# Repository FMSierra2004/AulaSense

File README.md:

# AulaSense

Repositorio principal para controlar el hardware, firmware y documentación de AulaSense.

## Estado actual

- Hardware: HW 0.1 DRAFT
- Firmware: FW 0.1.0-dev
- Etapa: planificación y prototipo inicial

## Organización

- `hardware/kicad`: esquema y PCB.
- `hardware/libraries`: símbolos y huellas propias.
- `hardware/manufacturing`: entregables para fabricación.
- `firmware`: código fuente del dispositivo.
- `docs`: arquitectura, planificación y compatibilidad.

## Versionado

El hardware utiliza versión y revisión física, por ejemplo `HW 1.0 Rev A`.

El firmware utiliza versiones `MAYOR.MENOR.CORRECCIÓN`, por ejemplo `FW 1.2.3`.

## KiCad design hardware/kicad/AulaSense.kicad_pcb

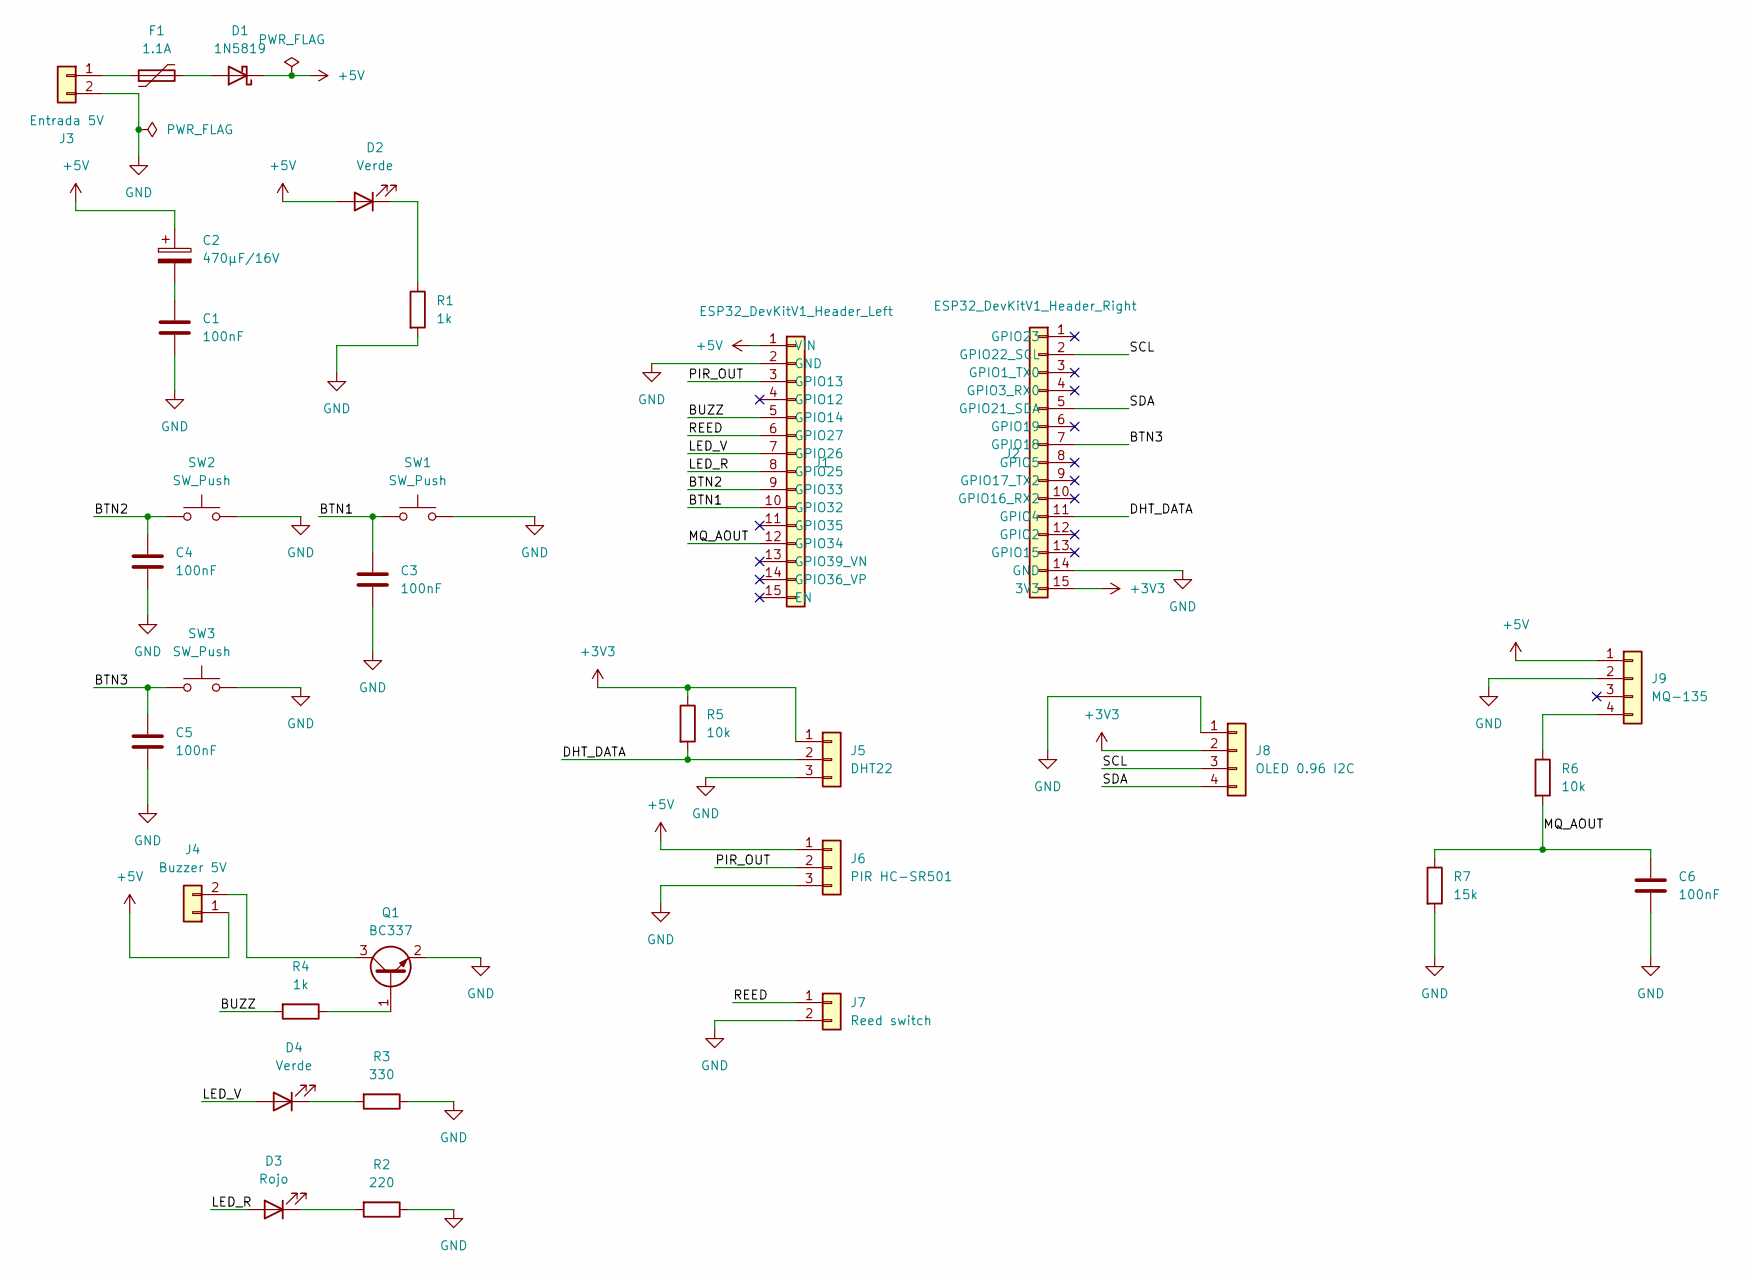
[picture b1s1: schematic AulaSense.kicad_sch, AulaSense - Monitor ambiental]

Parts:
C1, C3, C4, C5, C6: 100nF; C_Disc_D5.0mm_W2.5mm_P5.00mm
C2: 470µF/16V; CP_Radial_D8.0mm_P3.50mm
D1: 1N5819; D_DO-41_SOD81_P10.16mm_Horizontal
D2, D4: Verde; LED_D5.0mm
D3: Rojo; LED_D5.0mm
F1: 1.1A; Fuse_Bourns_MF-RG300
J1: ESP32_DevKitV1_Header_Left; PinSocket_1x15_P2.54mm_Vertical
J2: ESP32_DevKitV1_Header_Right; PinSocket_1x15_P2.54mm_Vertical
J3: Entrada 5V; PinHeader_1x02_P2.54mm_Vertical
J4: Buzzer 5V; PinHeader_1x02_P2.54mm_Vertical
J5: DHT22; PinHeader_1x03_P2.54mm_Vertical
J6: PIR HC-SR501; PinHeader_1x03_P2.54mm_Vertical
J7: Reed switch; PinHeader_1x02_P2.54mm_Vertical
J8: OLED 0.96 I2C; PinHeader_1x04_P2.54mm_Vertical
J9: MQ-135; PinHeader_1x04_P2.54mm_Vertical
Q1: BC337; TO-92_Inline
R1, R4: 1k; R_Axial_DIN0207_L6.3mm_D2.5mm_P10.16mm_Horizontal
R2: 220; R_Axial_DIN0207_L6.3mm_D2.5mm_P10.16mm_Horizontal
R3: 330; R_Axial_DIN0207_L6.3mm_D2.5mm_P10.16mm_Horizontal
R5, R6: 10k; R_Axial_DIN0207_L6.3mm_D2.5mm_P10.16mm_Horizontal
R7: 15k; R_Axial_DIN0207_L6.3mm_D2.5mm_P10.16mm_Horizontal
SW1, SW2, SW3: SW_Push; SW_PUSH_6mm

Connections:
+3V3: J2.15 (3V3), J5.1, J8.2, R5.1
+5V: C2.1, D1.1 (K), D2.2 (A), J1.1 (VIN), J4.1, J6.1, J9.1
/BTN1: C3.1, J1.10 (GPIO32), SW1.1
/BTN2: C4.1, J1.9 (GPIO33), SW2.1
/BTN3: C5.1, J2.7 (GPIO18), SW3.1
/BUZZ: J1.5 (GPIO14), R4.2
/DHT_DATA: J2.11 (GPIO4), J5.2, R5.2
/LED_R: D3.2 (A), J1.8 (GPIO25)
/LED_V: D4.2 (A), J1.7 (GPIO26)
/MQ_AOUT: C6.1, J1.12 (GPIO34), R6.2, R7.1
/PIR_OUT: J1.3 (GPIO13), J6.2
/REED: J1.6 (GPIO27), J7.1
/SCL: J2.2 (GPIO22_SCL), J8.3
/SDA: J2.5 (GPIO21_SDA), J8.4
GND: C1.2, C3.2, C4.2, C5.2, C6.2, J1.2 (GND), J2.14 (GND), J3.2, J5.3, J6.3, J7.2, J8.1, J9.2, Q1.2 (E), R1.2, R2.1, R3.1, R7.2, SW1.2, SW2.2, SW3.2
unnamed: C1.1, C2.2
unnamed: D1.2 (A), F1.2
unnamed: D2.1 (K), R1.1
unnamed: D3.1 (K), R2.2
unnamed: D4.1 (K), R3.2
unnamed: F1.1, J3.1
unnamed: J4.2, Q1.3 (C)
unnamed: J9.4, R6.1
unnamed: Q1.1 (B), R4.1

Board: 2 copper layers, 31 parts (0 on the bottom side), 24 nets, no tracks yet.

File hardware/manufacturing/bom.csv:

"Reference","Qty","Value","Footprint","Datasheet"
"C1,C3,C4,C5,C6","5","100nF","Capacitor_THT:C_Disc_D5.0mm_W2.5mm_P5.00mm",""
"C2","1","470µF/16V","Capacitor_THT:CP_Radial_D8.0mm_P3.50mm",""
"D1","1","SS34","Diode_THT:D_DO-41_SOD81_P10.16mm_Horizontal",""
"D2,D4","2","Verde","LED_THT:LED_D5.0mm",""
"D3","1","Rojo","LED_THT:LED_D5.0mm",""
"F1","1","1.1A","Resistor_THT:R_Axial_DIN0207_L6.3mm_D2.5mm_P7.62mm_Horizontal",""
"J1","1","ESP32_DevKitV1_Header_Left","Connector_PinSocket_2.54mm:PinSocket_1x15_P2.54mm_Vertical",""
"J2","1","ESP32_DevKitV1_Header_Right","Connector_PinSocket_2.54mm:PinSocket_1x15_P2.54mm_Vertical",""
"J3","1","Entrada 5V","Connector_PinHeader_2.54mm:PinHeader_1x02_P2.54mm_Vertical",""
"J4","1","Buzzer 5V","Connector_PinHeader_2.54mm:PinHeader_1x02_P2.54mm_Vertical",""
"J5","1","DHT22","Connector_PinHeader_2.54mm:PinHeader_1x03_P2.54mm_Vertical",""
"J6","1","PIR HC-SR501","Connector_PinHeader_2.54mm:PinHeader_1x03_P2.54mm_Vertical",""
"J7","1","Reed switch","Connector_PinHeader_2.54mm:PinHeader_1x02_P2.54mm_Vertical",""
"J8","1","OLED 0.96 I2C","Connector_PinHeader_2.54mm:PinHeader_1x04_P2.54mm_Vertical",""
"J9","1","MQ-135","Connector_PinHeader_2.54mm:PinHeader_1x04_P2.54mm_Vertical",""
"Q1","1","BC337","Package_TO_SOT_THT:TO-92_Inline",""
"R1,R4","2","1k","Resistor_THT:R_Axial_DIN0207_L6.3mm_D2.5mm_P10.16mm_Horizontal",""
"R2","1","220","Resistor_THT:R_Axial_DIN0207_L6.3mm_D2.5mm_P10.16mm_Horizontal",""
"R3","1","330","Resistor_THT:R_Axial_DIN0207_L6.3mm_D2.5mm_P10.16mm_Horizontal",""
"R5,R6","2","10k","Resistor_THT:R_Axial_DIN0207_L6.3mm_D2.5mm_P10.16mm_Horizontal",""
"R7","1","15k","Resistor_THT:R_Axial_DIN0207_L6.3mm_D2.5mm_P10.16mm_Horizontal",""
"SW1,SW2,SW3","3","SW_Push","Button_Switch_THT:SW_PUSH_6mm",""
